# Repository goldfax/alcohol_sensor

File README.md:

# alcohol_sensor
Breakout for the PSoC CY8CKIT-049 and the MQ-3 alcohol gas sensor with LED's representing ADC values.

### Needed Materials
All one needs for this is batteries, a 5V linear regulator (LDO), and LEDs plus matching resistors, and
the MQ-3 alcohol gas sensor. The MCU that runs this is the Cypress CY8CKIT-049, which just happens to be around
$4.00

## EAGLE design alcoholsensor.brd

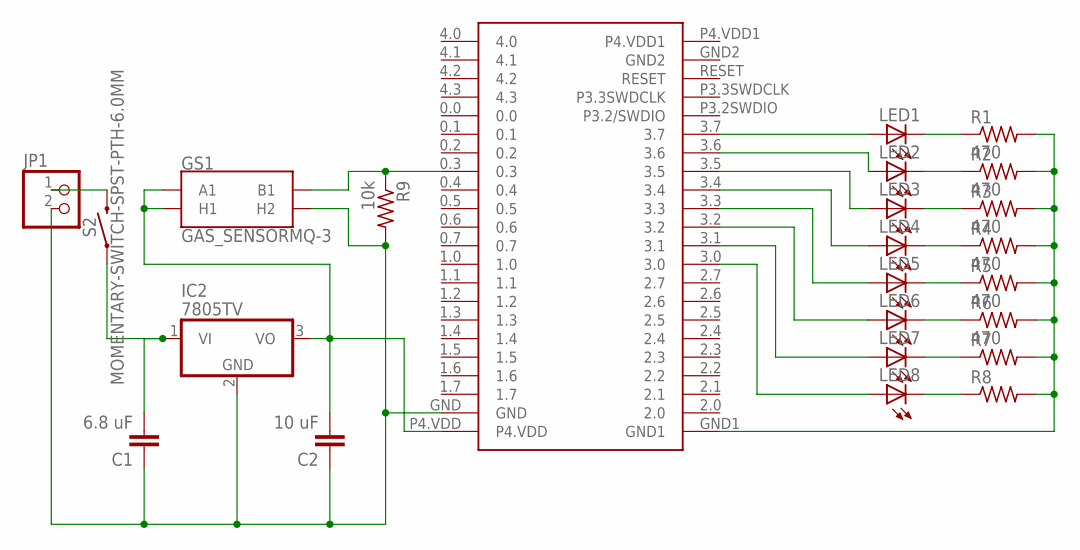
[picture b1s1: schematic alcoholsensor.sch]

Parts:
C1: 6.8 uF; C2.5-4
C2: 10 uF; C2.5-4
GS1: GAS_SENSORMQ-3; GAS_SENSOR
IC2: 7805TV; TO220V
JP1: PINHD-1X2; 1X02
LED1, LED2, LED3, LED4, LED5, LED6, LED7, LED8: LED5MM
R1, R2, R3, R4, R5, R6: 470; 0207/10
R7, R8: R-US_0207/10; 0207/10
R9: 10k; 0207/10
S2: MOMENTARY-SWITCH-SPST-PTH-6.0MM; TACTILE_SWITCH_PTH_6.0MM
U$1: CY8CKIT-049

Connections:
5V: C2.2, GS1.A1, GS1.HA (H1), IC2.3 (VO), U$1.P4.VDD
6V: C1.2, IC2.1 (VI), S2.1
BLUE: LED7.A, U$1.3.1
BLUE1: LED8.A, U$1.3.0
DATA: GS1.B1, R9.1, U$1.0.3
GND1: C1.1, C2.1, GS1.HB (H2), IC2.2 (GND), JP1.2, R9.2, U$1.GND
GND2: R1.2, R2.2, R3.2, R4.2, R5.2, R6.2, R7.2, R8.2, U$1.GND1
GREEN: LED5.A, U$1.3.3
GREEN1: LED6.A, U$1.3.2
unnamed: JP1.1, S2.3 (2)
unnamed: LED1.K (C), R1.1
unnamed: LED2.K (C), R2.1
unnamed: LED3.K (C), R3.1
unnamed: LED4.K (C), R4.1
unnamed: LED5.K (C), R5.1
unnamed: LED6.K (C), R6.1
unnamed: LED7.K (C), R7.1
unnamed: LED8.K (C), R8.1
ORANGE: LED3.A, U$1.3.5
ORANGE1: LED4.A, U$1.3.4
RED: LED1.A, U$1.3.7
RED1: LED2.A, U$1.3.6

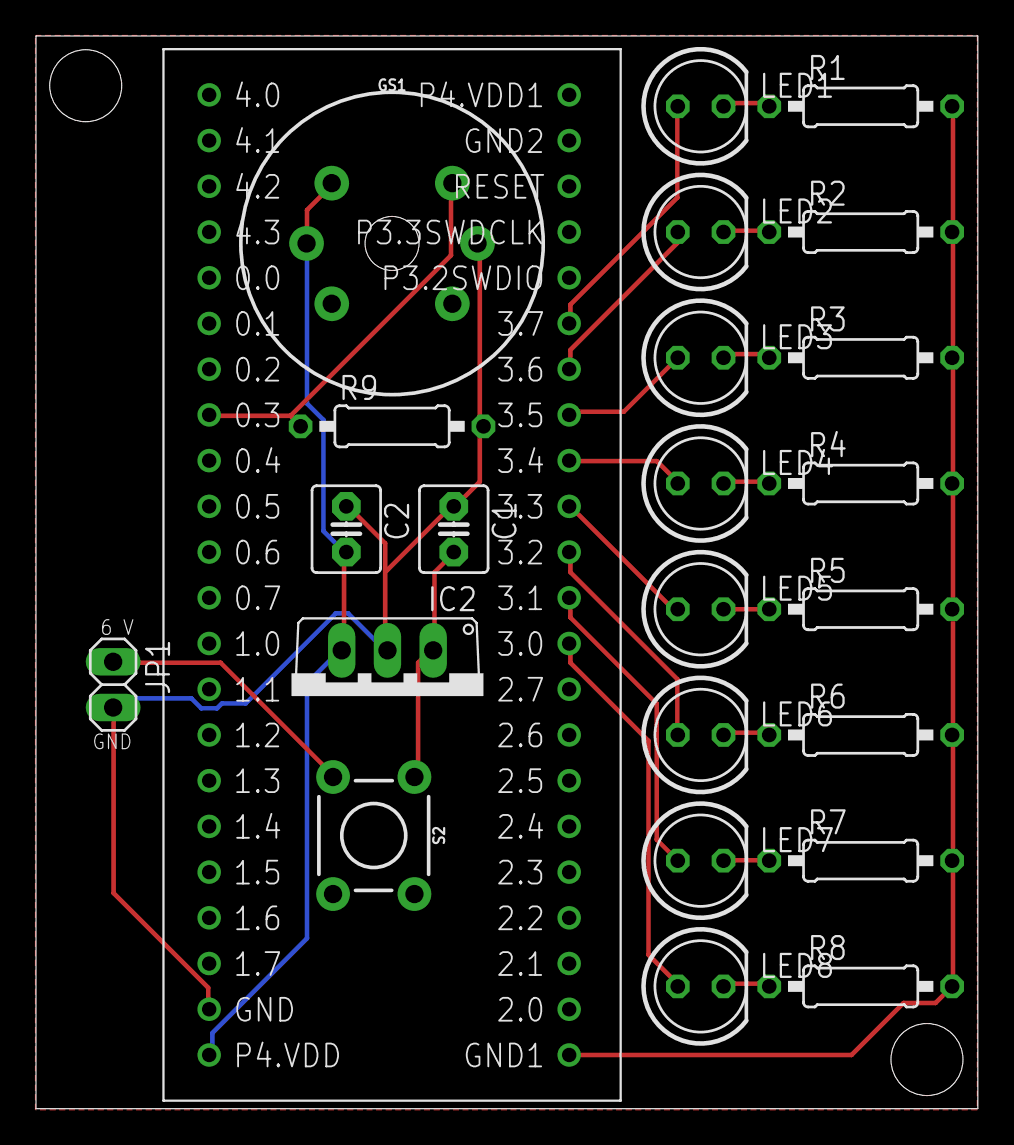
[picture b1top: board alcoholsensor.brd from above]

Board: 2 copper layers, 52.3 x 59.6 mm, 24 parts (0 on the bottom side), 22 nets.

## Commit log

2017-03-23 restructured files
2017-03-23 Created images
2017-03-24 Improved design (made smaller)
2017-03-26 Added mount points to board
2017-04-02 Added pushbutton switch to control power source

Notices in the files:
parts and their libraries:
SparkFun-Sensors: Licensing: Creative Commons ShareAlike 4.0 International - https://creativecommons.org/licenses/by-sa/4.0
